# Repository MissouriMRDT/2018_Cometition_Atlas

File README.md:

# 2018_Cometition_Atlas
All Hardware and Software Files used in the 2018 Competition

How to add repos to this while retaining commit history:

1. Clone this repo onto your pc
2. Make branch on here for the repo you're about to copy in
3. Make sure that you've merged the final release branch of the target repo into master
4. In gitshell inside of the 2018 Competition Atlas folder:

git checkout [name of branch you're going to copy the repo into]

git remote add x [url of deprecated repo]

git fetch x

git merge x/master --allow-unrelated-histories

git remote rm x

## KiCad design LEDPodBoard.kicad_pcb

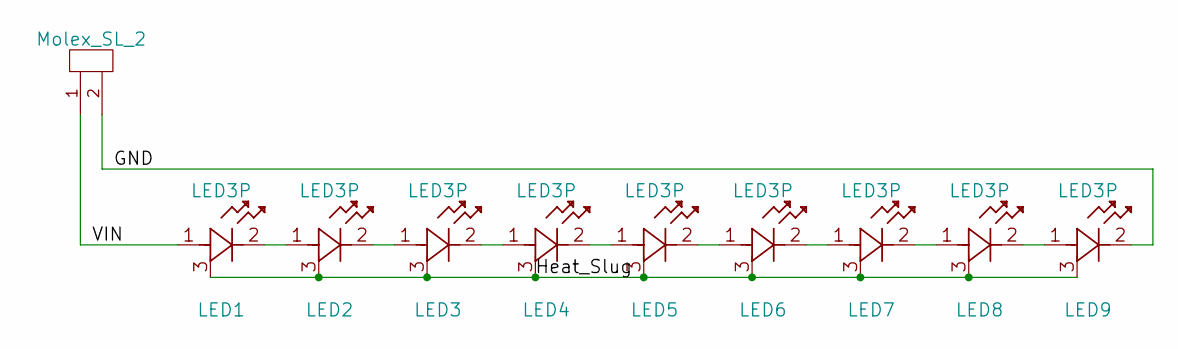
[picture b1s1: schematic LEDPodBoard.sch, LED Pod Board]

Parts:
Conn1: Molex_SL_2; MOLEX_SL_2_Horizontal
LED1, LED2, LED3, LED4, LED5, LED6, LED7, LED8, LED9: LED3P; LED_CREE_XLAMP_XPG

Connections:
/GND: Conn1.2, LED9.2 (Cathode)
/Heat_Slug: LED1.3 (Heat_Dissipation), LED2.3 (Heat_Dissipation), LED3.3 (Heat_Dissipation), LED4.3 (Heat_Dissipation), LED5.3 (Heat_Dissipation), LED6.3 (Heat_Dissipation), LED7.3 (Heat_Dissipation), LED8.3 (Heat_Dissipation), LED9.3 (Heat_Dissipation)
/VIN: Conn1.1, LED1.1 (Anode)
unnamed: LED1.2 (Cathode), LED2.1 (Anode)
unnamed: LED2.2 (Cathode), LED3.1 (Anode)
unnamed: LED3.2 (Cathode), LED4.1 (Anode)
unnamed: LED4.2 (Cathode), LED5.1 (Anode)
unnamed: LED5.2 (Cathode), LED6.1 (Anode)
unnamed: LED6.2 (Cathode), LED7.1 (Anode)
unnamed: LED7.2 (Cathode), LED8.1 (Anode)
unnamed: LED8.2 (Cathode), LED9.1 (Anode)

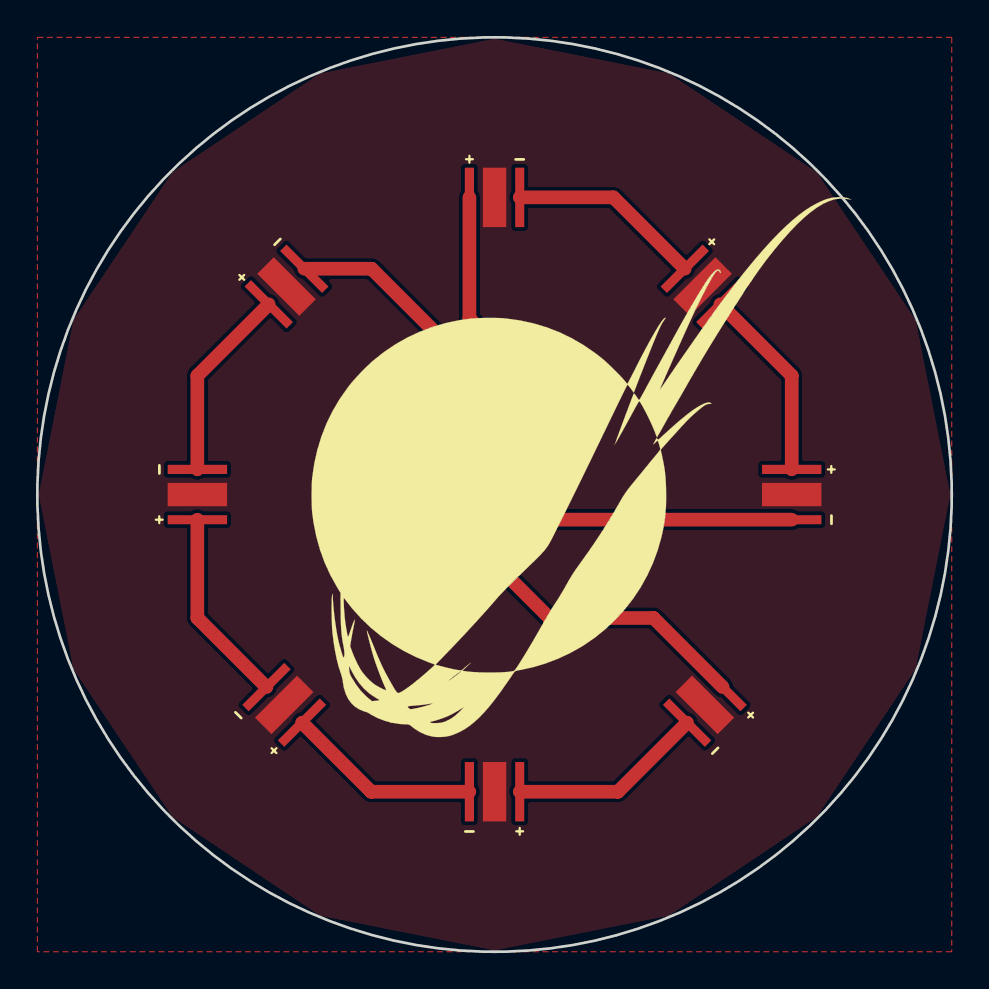
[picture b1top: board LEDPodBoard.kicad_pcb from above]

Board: 2 copper layers, 50.8 x 50.8 mm, 10 parts (1 on the bottom side), 11 nets.

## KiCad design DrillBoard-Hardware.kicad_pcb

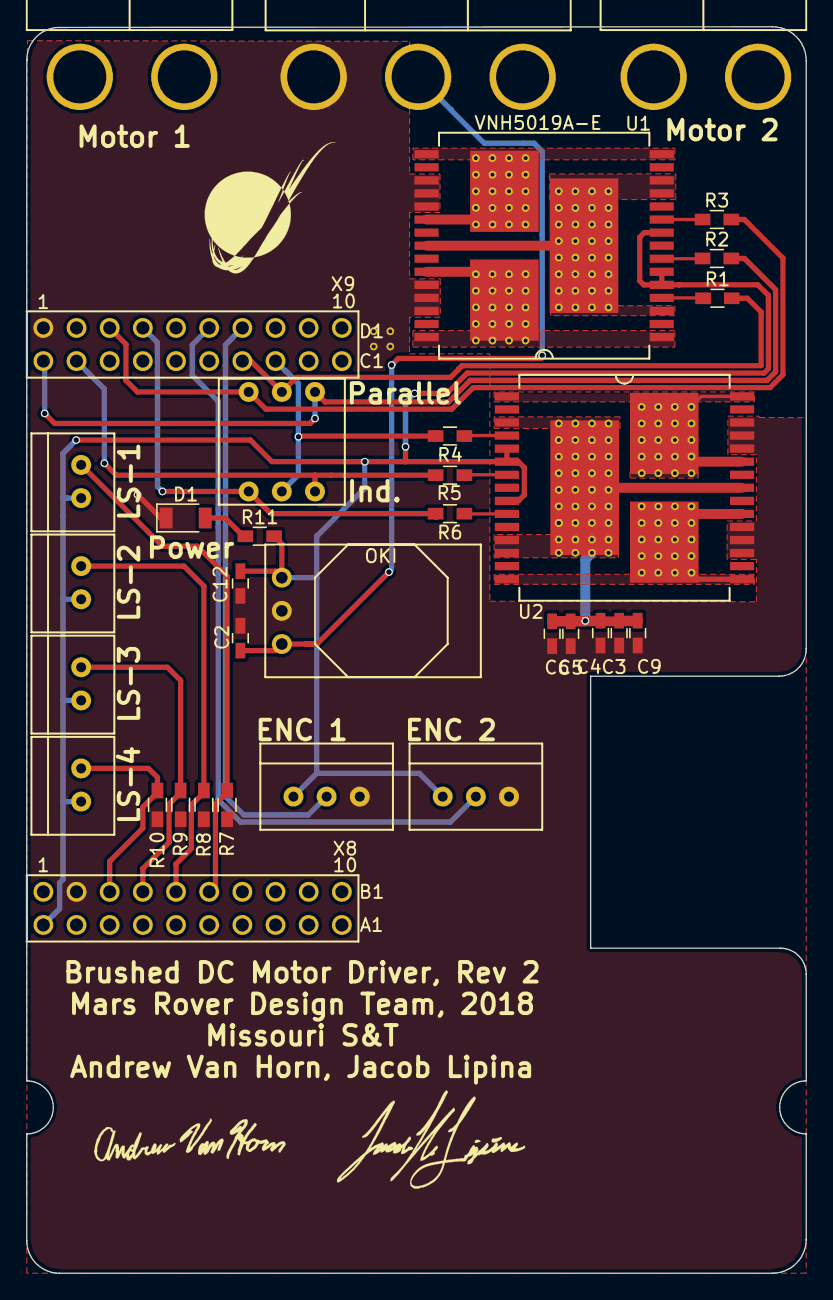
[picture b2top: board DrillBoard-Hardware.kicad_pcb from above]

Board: 2 copper layers, 59.7 x 95.5 mm, 33 parts (0 on the bottom side), 27 nets.

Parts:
C1: Anderson_3; Anderson_3_Horisontal_Side_by_Side
C2, C3, C5, C6, C9, C12: 10u; C_0603_HandSoldering
C4: .1u; C_0603_HandSoldering
C7, C8: Anderson-2; Anderson_2_Horisontal_Side_by_Side
D1: LED; D_1206
R1, R2, R3, R4, R5, R6: 1K; R_0603_HandSoldering
R7, R8, R9, R10: 10K; R_0603_HandSoldering
R11: 330; R_0603_HandSoldering
SW1: 3P1T_Fused; 3P1T_Switch
U1, U2: VNH5019A-E; MultiPowerSO_30
U3: OKI; OKI_Horisontal
U4: LS_1; MOLEX_SL_2_Vertical
U5: LS_2; MOLEX_SL_2_Vertical
U6: TM4C129E_Launchpad_X9
U7, U8: Picoblade-3; MOLEX_SL_3_Vertical
U9: LS_3; MOLEX_SL_2_Vertical
U10: LS_4; MOLEX_SL_2_Vertical

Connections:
+3V3: C12.1, R11.2, U1.5, U1.6, U1.9, U2.5, U2.6, U2.9, U3.3, U4.1, U5.1, U6.+3V3, U7.1, U8.1, U9.1, U10.1
+12V: C1.1, C3.1, C4.1, C5.1, C6.1, C9.1, U1.3, U1.12, U1.13, U1.23, U1.32, U2.3, U2.12, U2.13, U2.23, U2.32
/12V_Logic: C1.2, C2.1, U3.1
/Out_A1: C7.1, U1.1, U1.25, U1.30, U1.31
/Out_A2: C8.1, U2.1, U2.25, U2.30, U2.31
/Out_B1: C7.2, U1.15, U1.16, U1.21, U1.33
/Out_B2: C8.2, U2.15, U2.16, U2.21, U2.33
Encoder1_PWM: U6.PD0, U7.2
Encoder2_PWM: U6.PD1, U8.2
GND: C1.3, C2.2, C3.2, C4.2, C5.2, C6.2, C9.2, C12.2, D1.1, R7.2, R8.2, R9.2, R10.2, U1.18, U1.19, U1.20, U1.26, U1.27, U1.28, U2.18, U2.19, U2.20, U2.26, U2.27, U2.28, U3.2, U6.GND, U7.3, U8.3
IN_A1: R1.2, SW1.3, U6.PL0
IN_A2: R4.2, SW1.4, U6.PL1
IN_B1: R3.2, SW1.1, U6.PH2
IN_B2: R6.2, SW1.2, U6.PH3
LS_1: R7.1, U4.2, U6.PE3
LS_2: R8.1, U5.2, U6.PE2
LS_3: R9.1, U6.PE1, U9.2
LS_4: R10.1, U6.PE0, U10.2
unnamed: D1.2, R11.1
unnamed: R1.1, U1.4
unnamed: R2.1, U1.7
unnamed: R3.1, U1.10
unnamed: R4.1, U2.4
unnamed: R5.1, U2.7
unnamed: R6.1, U2.10
PWM1: R2.2, SW1.5, U6.PF1
PWM2: R5.2, SW1.6, U6.PF2

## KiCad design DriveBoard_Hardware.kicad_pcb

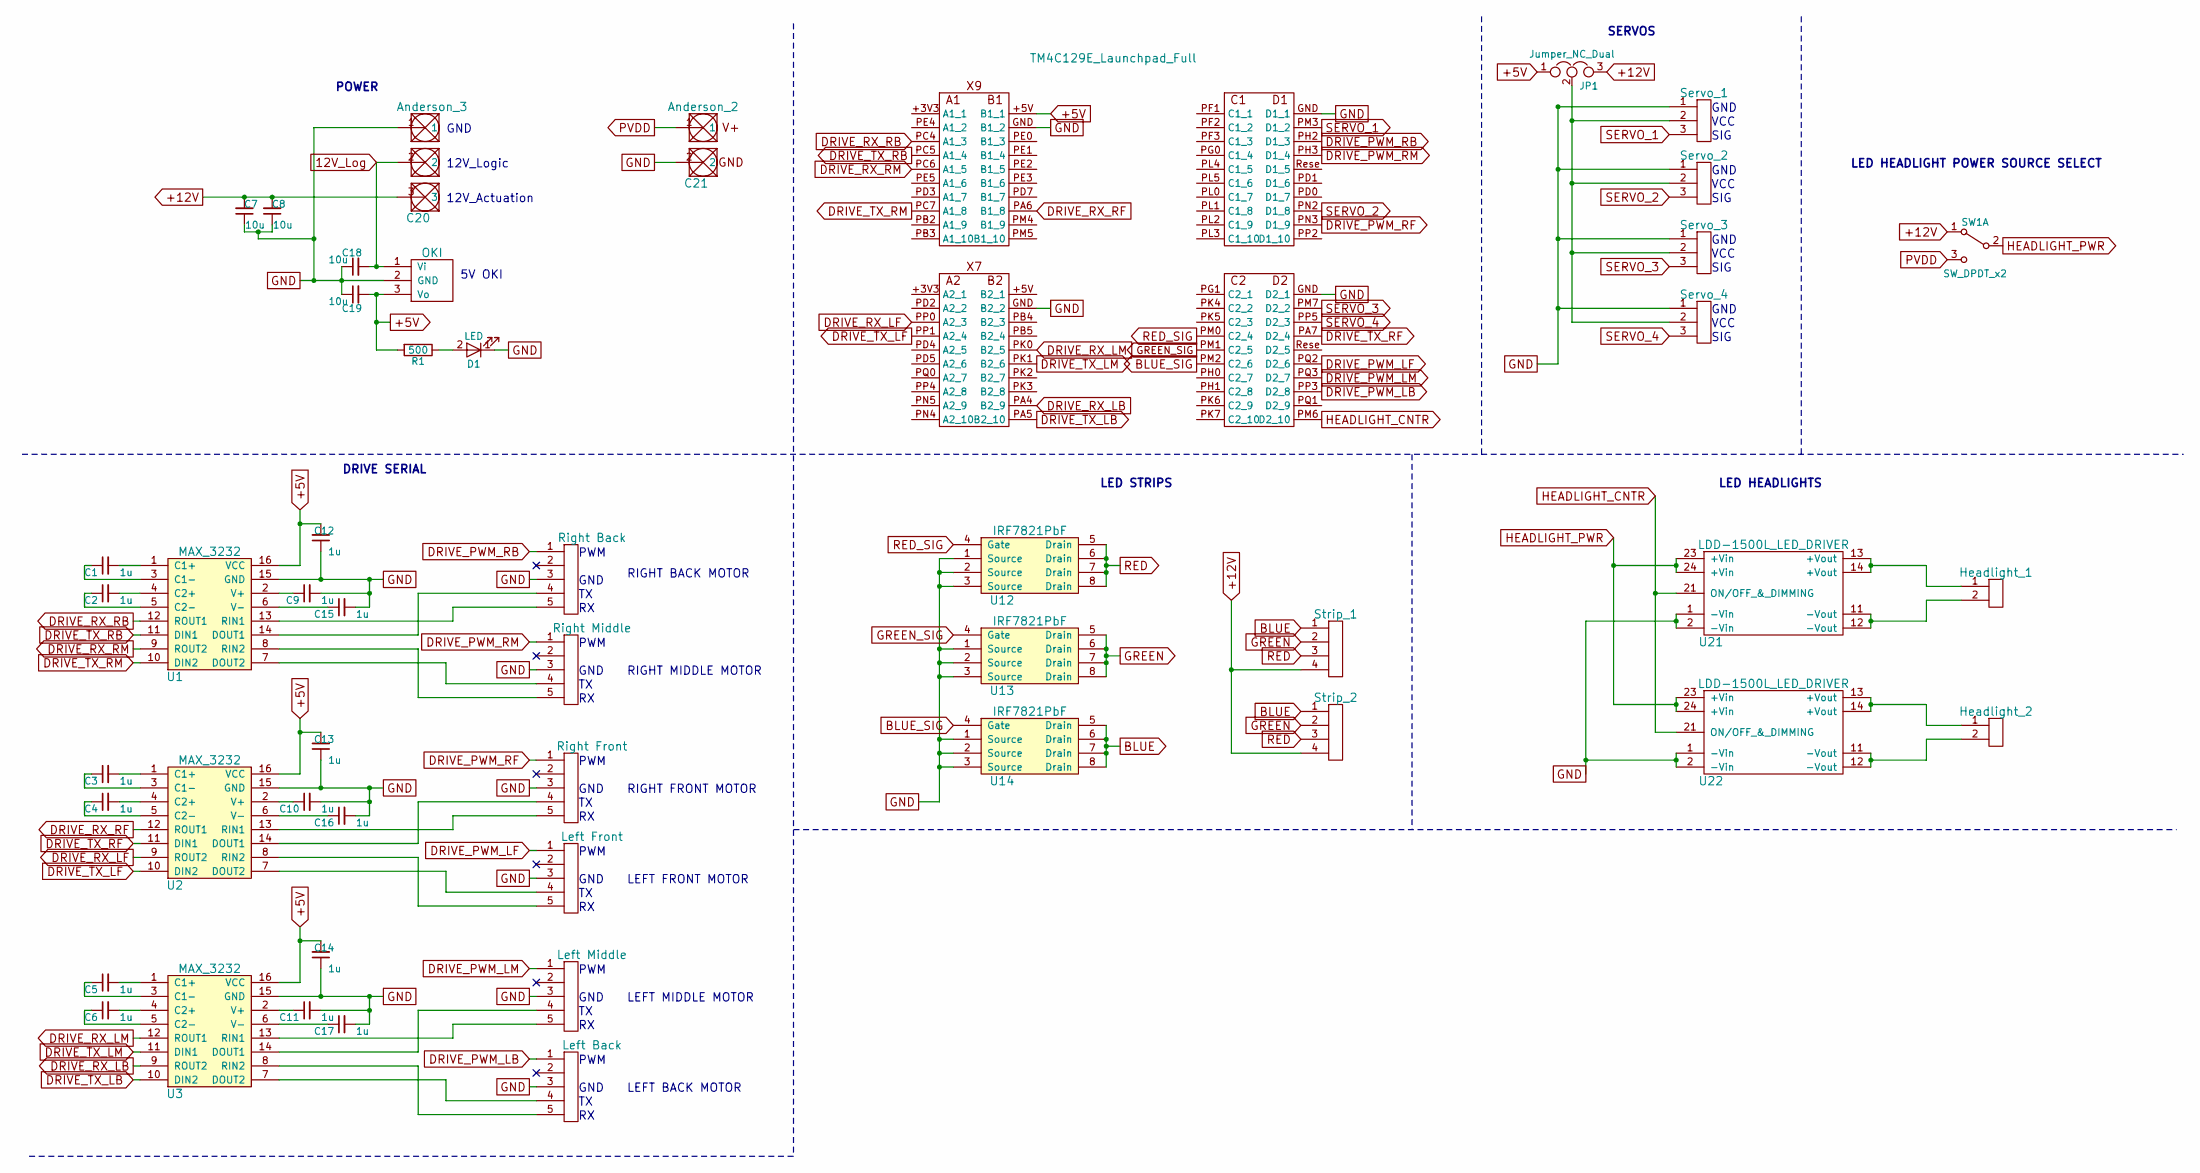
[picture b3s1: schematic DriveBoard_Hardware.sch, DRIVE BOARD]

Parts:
C1, C2, C3, C4, C5, C6, C9, C10, C11, C12, C13, C14, C15, C16, C17: 1u; C_0603_HandSoldering
C7, C8, C18, C19: 10u; C_0603_HandSoldering
C20: Anderson_3; Anderson_3_Horisontal_Side_by_Side
C21: Anderson_2; Anderson_2_Horisontal_Side_by_Side
D1: LED; LED_1206_HandSoldering
JP1: Jumper_NC_Dual; Pin_Header_Angled_1x03_Pitch1.27mm
R1: 500; R_0603_HandSoldering
SW1: SW_DPDT_x2; 1P2T_Angled_Slide_GPI-152-3013
U1, U2, U3: MAX_3232; SOIC_16_3.9x9.9mm_Pitch1.27mm
U4: OKI; OKI_Horisontal
U5: Right Back; MOLEX_SL_5_Horizontal
U6: Right Middle; MOLEX_SL_5_Horizontal
U7: Right Front; MOLEX_SL_5_Horizontal
U8: Left Front; MOLEX_SL_5_Horizontal
U9: Left Middle; MOLEX_SL_5_Horizontal
U10: Left Back; MOLEX_SL_5_Horizontal
U11: TM4C129E_Launchpad_Full; TM4C129E_Launchpad_FULL_Booster_Bottom_SMD
U12, U13, U14: IRF7821PbF; SO-8_5.3x6.2mm_Pitch1.27mm
U15: Strip_1; MOLEX_SL_4_Horizontal
U16: Strip_2; MOLEX_SL_4_Horizontal
U17: Servo_1; MOLEX_SL_3_Vertical
U18: Servo_2; MOLEX_SL_3_Vertical
U19: Servo_3; MOLEX_SL_3_Vertical
U20: Servo_4; MOLEX_SL_3_Vertical
U21, U22: LDD-1500L_LED_DRIVER
U23: Headlight_1; MOLEX_SL_2_Vertical
U24: Headlight_2; MOLEX_SL_2_Vertical

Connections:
12V_Log: C18.2, C20.2, U4.1 (Vi)
+5V: C12.2, C13.2, C14.2, C19.2, JP1.1, R1.2, U1.16 (VCC), U2.16 (VCC), U3.16 (VCC), U4.3 (Vo), U11.+5V (B1_1)
+12V: C7.2, C8.2, C20.3, JP1.3, SW1.1 (A), U15.4, U16.4
BLUE: U14.5 (Drain), U14.6 (Drain), U14.7 (Drain), U14.8 (Drain), U15.1, U16.1
BLUE_SIG: U11.PM2 (C2_6), U14.4 (Gate)
DRIVE_PWM_LB: U10.1, U11.PP3 (D2_8)
DRIVE_PWM_LF: U8.1, U11.PQ2 (D2_6)
DRIVE_PWM_LM: U9.1, U11.PQ3 (D2_7)
DRIVE_PWM_RB: U5.1, U11.PH2 (D1_3)
DRIVE_PWM_RF: U7.1, U11.PN3 (D1_9)
DRIVE_PWM_RM: U6.1, U11.PH3 (D1_4)
DRIVE_RX_LB: U3.9 (ROUT2), U11.PA4 (B2_9)
DRIVE_RX_LF: U2.9 (ROUT2), U11.PP0 (A2_3)
DRIVE_RX_LM: U3.12 (ROUT1), U11.PK0 (B2_5)
DRIVE_RX_RB: U1.12 (ROUT1), U11.PC4 (A1_3)
DRIVE_RX_RF: U2.12 (ROUT1), U11.PA6 (B1_8)
DRIVE_RX_RM: U1.9 (ROUT2), U11.PC6 (A1_5)
DRIVE_TX_LB: U3.10 (DIN2), U11.PA5 (B2_10)
DRIVE_TX_LF: U2.10 (DIN2), U11.PP1 (A2_4)
DRIVE_TX_LM: U3.11 (DIN1), U11.PK1 (B2_6)
DRIVE_TX_RB: U1.11 (DIN1), U11.PC5 (A1_4)
DRIVE_TX_RF: U2.11 (DIN1), U11.PA7 (D2_4)
DRIVE_TX_RM: U1.10 (DIN2), U11.PC7 (A1_8)
GND: C7.1, C8.1, C9.2, C10.2, C11.2, C12.1, C13.1, C14.1, C15.2, C16.2, C17.2, C18.1, C19.1, C20.1, C21.2, D1.1 (K), U1.15 (GND), U2.15 (GND), U3.15 (GND), U4.2 (GND), U5.3, U6.3, U7.3, U8.3, U9.3, U10.3, U11.GND (B1_2), U12.1 (Source), U12.2 (Source), U12.3 (Source), U13.1 (Source), U13.2 (Source), U13.3 (Source), U14.1 (Source), U14.2 (Source), U14.3 (Source), U17.1, U18.1, U19.1, U20.1, U21.1 (-Vin), U21.2 (-Vin), U22.1 (-Vin), U22.2 (-Vin)
GREEN: U13.5 (Drain), U13.6 (Drain), U13.7 (Drain), U13.8 (Drain), U15.2, U16.2
GREEN_SIG: U11.PM1 (C2_5), U13.4 (Gate)
HEADLIGHT_CNTR: U11.PM6 (D2_10), U21.21 (ON/OFF_&_DIMMING), U22.21 (ON/OFF_&_DIMMING)
HEADLIGHT_PWR: SW1.2 (B), U21.23 (+Vin), U21.24 (+Vin), U22.23 (+Vin), U22.24 (+Vin)
unnamed: C1.1, U1.3 (C1-)
unnamed: C1.2, U1.1 (C1+)
unnamed: C2.1, U1.5 (C2-)
unnamed: C2.2, U1.4 (C2+)
unnamed: C3.1, U2.3 (C1-)
unnamed: C3.2, U2.1 (C1+)
unnamed: C4.1, U2.5 (C2-)
unnamed: C4.2, U2.4 (C2+)
unnamed: C5.1, U3.3 (C1-)
unnamed: C5.2, U3.1 (C1+)
unnamed: C6.1, U3.5 (C2-)
unnamed: C6.2, U3.4 (C2+)
unnamed: C9.1, U1.2 (V+)
unnamed: C10.1, U2.2 (V+)
unnamed: C11.1, U3.2 (V+)
unnamed: C15.1, U1.6 (V-)
unnamed: C16.1, U2.6 (V-)
unnamed: C17.1, U3.6 (V-)
unnamed: D1.2 (A), R1.1
unnamed: JP1.2, U17.2, U18.2, U19.2, U20.2
unnamed: U1.7 (DOUT2), U6.4
unnamed: U1.8 (RIN2), U6.5
unnamed: U1.13 (RIN1), U5.5
unnamed: U1.14 (DOUT1), U5.4
unnamed: U2.7 (DOUT2), U8.4
unnamed: U2.8 (RIN2), U8.5
unnamed: U2.13 (RIN1), U7.5
unnamed: U2.14 (DOUT1), U7.4
unnamed: U3.13 (RIN1), U9.5
unnamed: U3.14 (DOUT1), U9.4
unnamed: U3.7 (DOUT2), U10.4
unnamed: U3.8 (RIN2), U10.5
unnamed: U21.11 (-Vout), U21.12 (-Vout), U23.2
unnamed: U21.13 (+Vout), U21.14 (+Vout), U23.1
unnamed: U22.11 (-Vout), U22.12 (-Vout), U24.2
unnamed: U22.13 (+Vout), U22.14 (+Vout), U24.1
PVDD: C21.1, SW1.3 (C)
RED: U12.5 (Drain), U12.6 (Drain), U12.7 (Drain), U12.8 (Drain), U15.3, U16.3
RED_SIG: U11.PM0 (C2_4), U12.4 (Gate)
SERVO_1: U11.PM3 (D1_2), U17.3
SERVO_2: U11.PN2 (D1_8), U18.3
SERVO_3: U11.PM7 (D2_2), U19.3
SERVO_4: U11.PP5 (D2_3), U20.3

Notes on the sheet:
GND
12V_Logic
12V_Actuation
5V OKI
POWER
PWM
RIGHT BACK MOTOR
RIGHT MIDDLE MOTOR
RIGHT FRONT MOTOR
LEFT FRONT MOTOR
LEFT MIDDLE MOTOR
LEFT BACK MOTOR
DRIVE SERIAL
VCC
SIG
SERVOS
LED STRIPS
LED HEADLIGHTS
LED HEADLIGHT POWER SOURCE SELECT

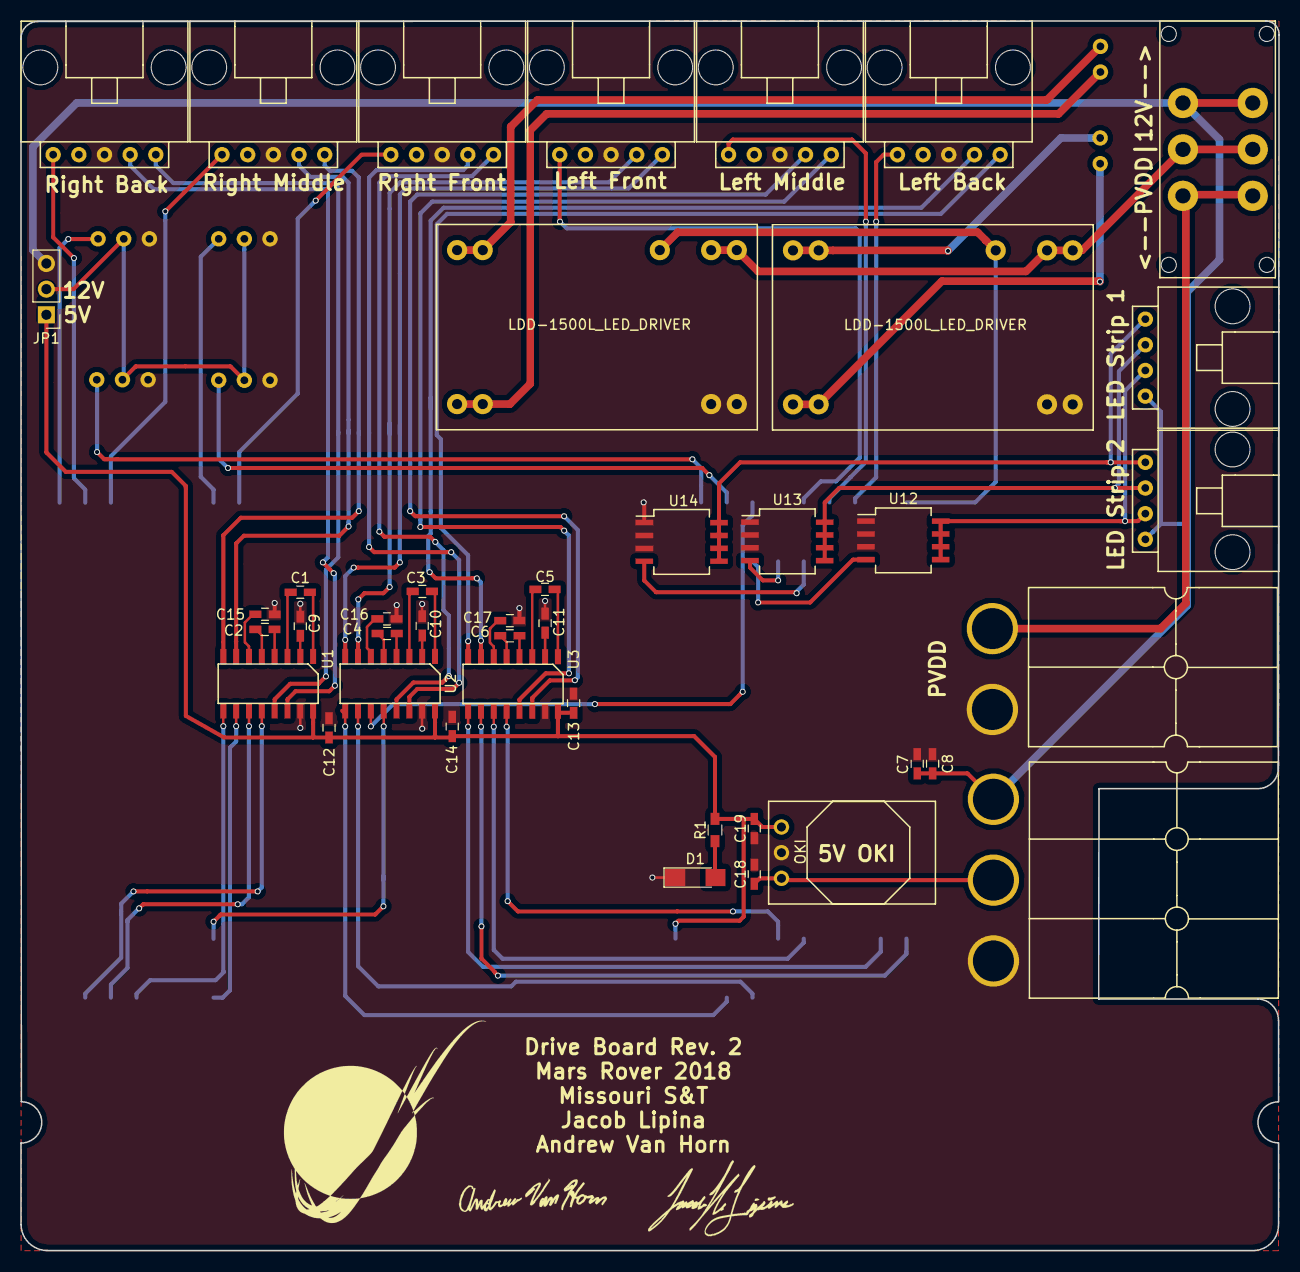
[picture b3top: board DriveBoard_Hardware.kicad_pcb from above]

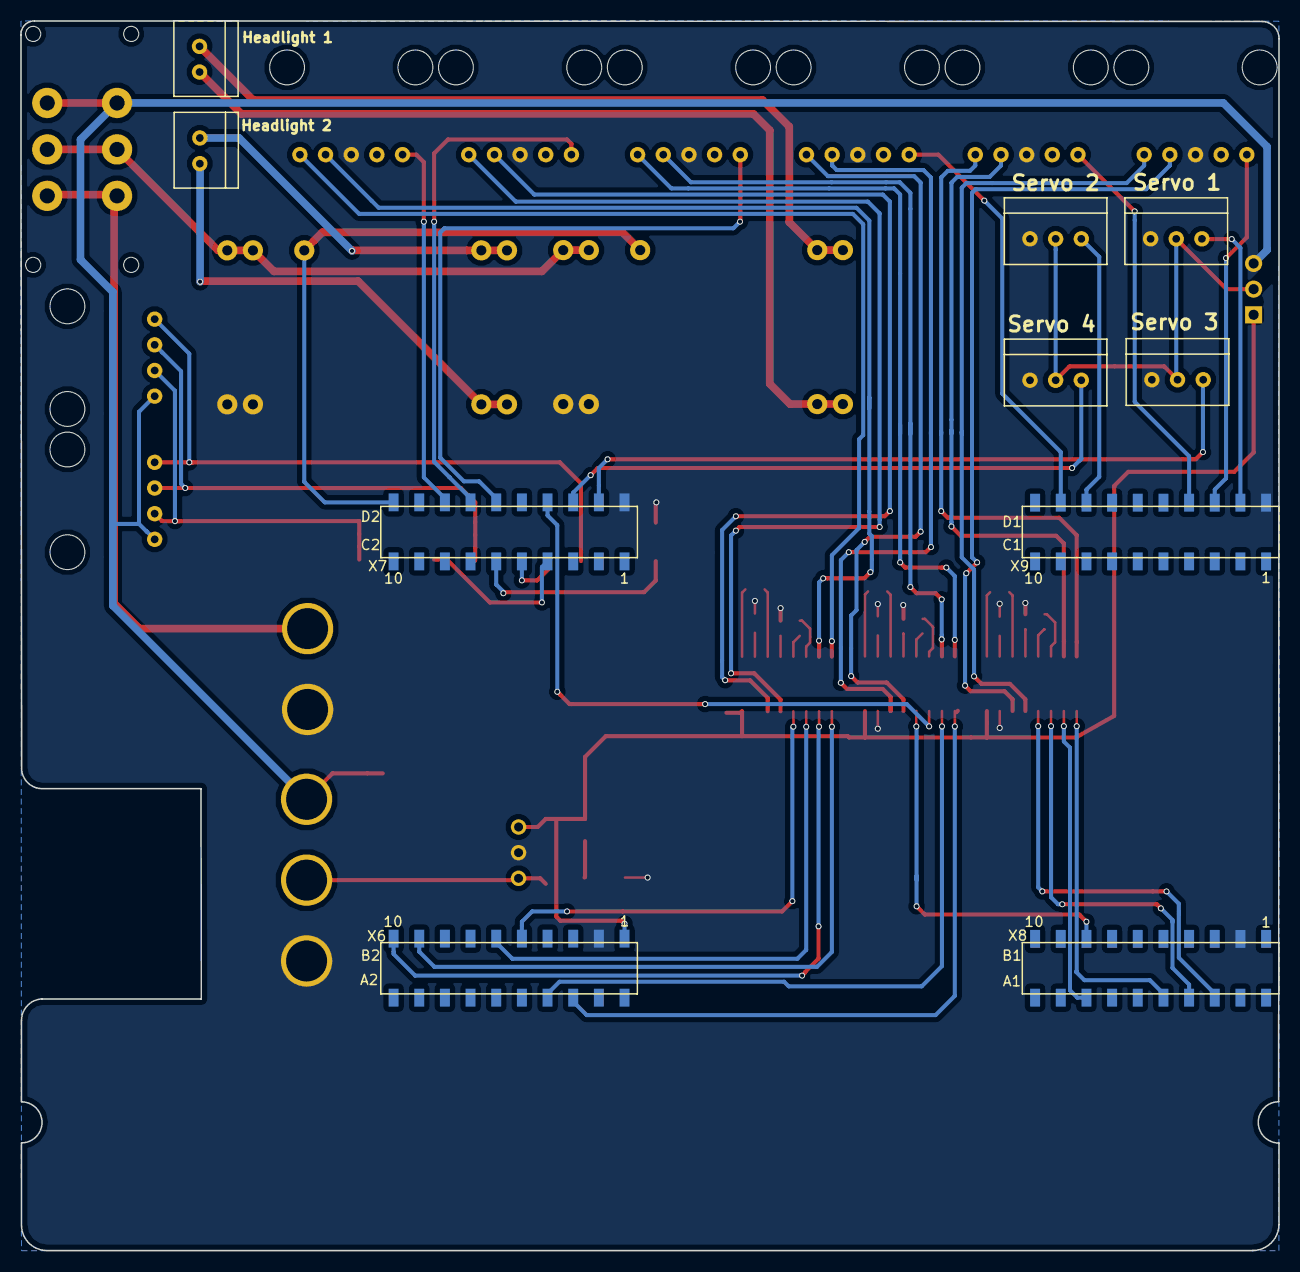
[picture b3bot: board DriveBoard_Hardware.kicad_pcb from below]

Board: 2 copper layers, 124.5 x 121.7 mm, 49 parts (6 on the bottom side), 71 nets.

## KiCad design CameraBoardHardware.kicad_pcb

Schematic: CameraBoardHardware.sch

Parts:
C2, C3, C4, C5, C6, C7, C9, C10, C11, C12, C13, C14, C15, C16, C17: 10uf; C_0603_HandSoldering
C8: Anderson_3; Anderson_3_Horisontal_Side_by_Side
C18, C19, C20: 0.1uf; C_0603_HandSoldering
D1: LED; LED_0603_HandSoldering
J1: BNC_75_OHM_HORIZ; BNC-75-Ohm-HORIZONTAL-1-1478032-0
J2, J3, J4, J5: BNC_75_OHM_HORIZ; bnc-ci
R1, R2, R3, R4, R9: 75; R_0603_HandSoldering
R5: 330; R_0603_HandSoldering
R6: 100k; R_0603_HandSoldering
R7, R8: 470; R_0603_HandSoldering
U1, U2, U3, U4, U14: Picoblade_3; Molex_PicoBlade_53047-0310_03x1.25mm_Straight
U5, U6, U7, U8: Molex_SL_3; MOLEX_SL_3_Vertical
U9: OKI; OKI_Horisontal
U10: LMH6574MA; LMH6574MA&slash_NOPB
U11: TM4C129E_Launchpad_X7; TM4C129E_Launchpad_X7_Bottom_SMD
U12: TXB0102_DCU_8; TXB0102DCUR
U13: Molex_SL_3; MOLEX_SL_3_Horizontal

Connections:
3.3V: C2.1, C5.1, C9.1, C12.1, C15.1, C18.1, R5.2, R6.2, U11.+3V3, U12.3
5V: C3.1, C6.1, C10.1, C13.1, C16.1, C19.1, U9.3 (Vo), U11.+5V, U12.7
12V: C4.1, C7.1, C8.2, C11.1, C14.1, C17.1, C20.1, U1.3, U2.3, U3.3, U4.3, U5.3, U6.3, U7.3, U8.3, U9.1 (Vi), U10.14, U13.2, U14.2
12VA: C8.3, U13.1, U14.3
A1: U11.PK4, U12.5
A2: U11.PK5, U12.4
B1: U10.8, U12.8
B2: U10.9, U12.1
Camera1_In: J4.1, R1.1, U4.1, U8.1, U10.1
Camera2_In: J3.1, R2.1, U3.1, U7.1, U10.3
Camera3_In: J2.1, R3.1, U2.1, U6.1, U10.5
Camera4_In: J5.1, R4.1, U1.1, U5.1, U10.7
Gnd: C2.2, C3.2, C4.2, C5.2, C6.2, C7.2, C8.1, C9.2, C10.2, C11.2, C12.2, C13.2, C14.2, C15.2, C16.2, C17.2, C18.2, C19.2, C20.2, D1.1 (K), J1.2, J2.2, J3.2, J4.2, J5.2, R1.2, R2.2, R3.2, R4.2, R6.1, R8.2, U1.2, U2.2, U3.2, U4.2, U5.2, U6.2, U7.2, U8.2, U9.2 (GND), U10.2, U10.4, U10.6, U10.10, U10.11, U11.GND, U12.2, U13.3, U14.1
unnamed: D1.2 (A), R5.1
unnamed: R7.1, R9.1, U10.13
unnamed: R7.2, R8.1, U10.12
OE: U11.PG1, U12.6
Video_Out: J1.1, R9.2

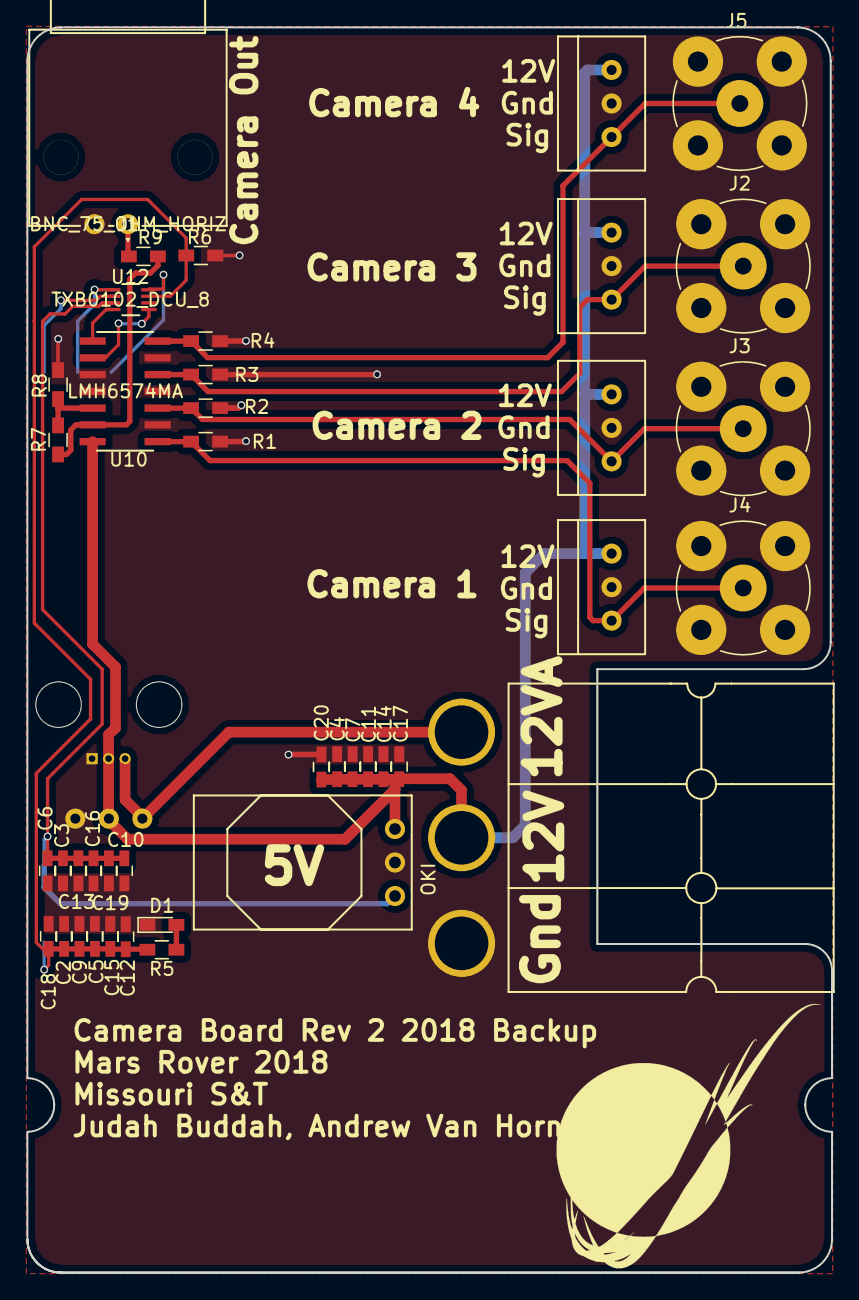
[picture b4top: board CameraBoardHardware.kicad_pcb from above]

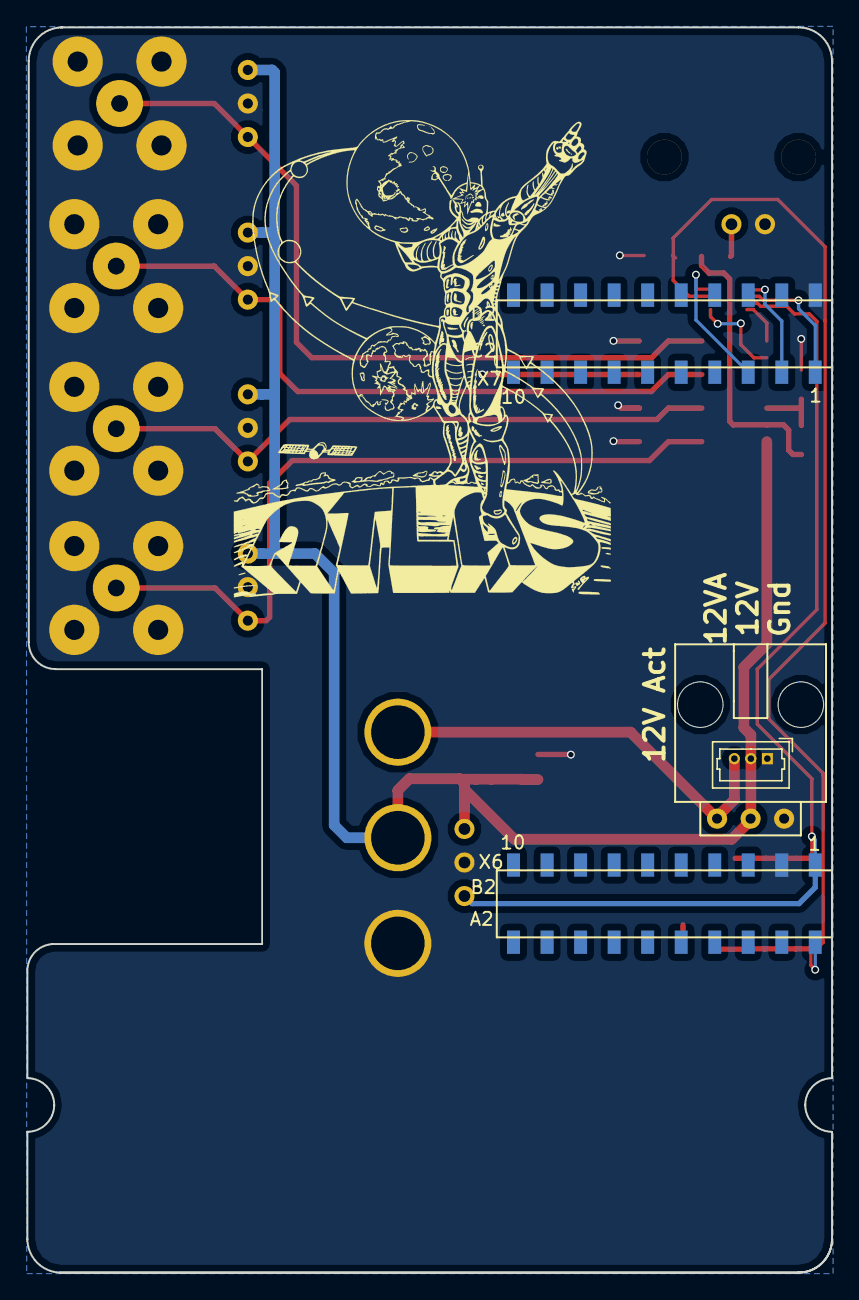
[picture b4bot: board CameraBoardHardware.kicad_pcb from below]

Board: 2 copper layers, 61.0 x 94.3 mm, 44 parts (2 on the bottom side), 18 nets.

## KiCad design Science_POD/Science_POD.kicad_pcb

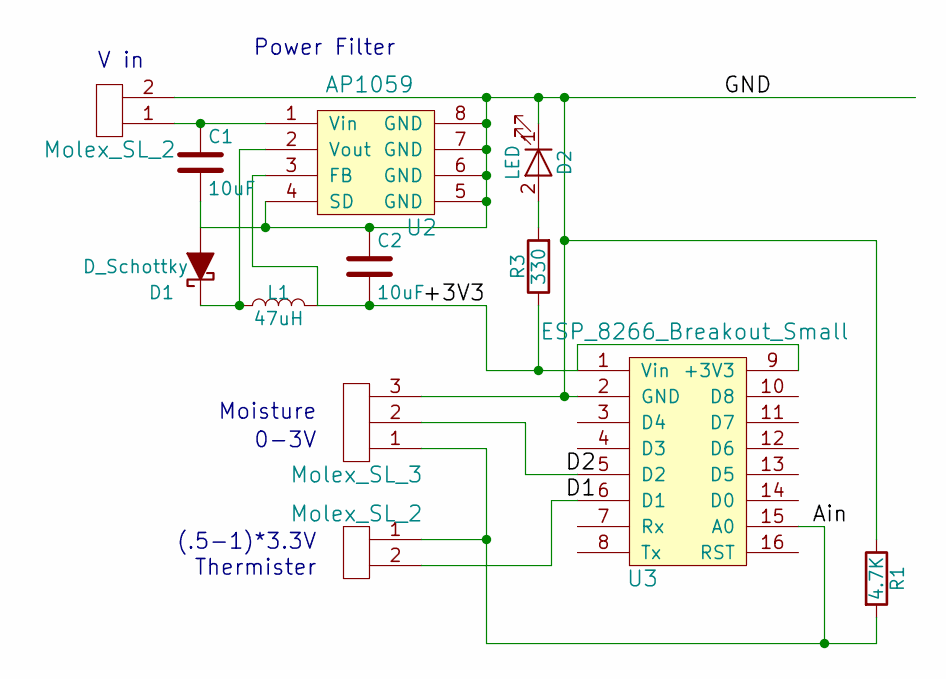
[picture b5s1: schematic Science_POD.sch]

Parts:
C1, C2: 10uF; C_0603_HandSoldering
Conn1: Molex_SL_2; MOLEX_SL_2_Horizontal
D1: D_Schottky; C_0603_HandSoldering
D2: LED; D_1206
L1: 47uH; L_0603_HandSoldering
R1: 4.7K; R_0603_HandSoldering
R3: 330; R_0603_HandSoldering
U1: Molex_SL_2; MOLEX_SL_2
U2: AP1059; HTSOP-8-1EP_3.9x4.9mm_Pitch1.27mm
U3: ESP_8266_Breakout_Small
U4: Molex_SL_3; MOLEX_SL_3

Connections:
/+3V3: C2.2, L1.2, R3.1, U2.3 (FB), U3.1 (Vin), U3.9 (+3V3)
/Ain: Conn1.1, R1.2, U3.15 (A0), U4.1
/D1: Conn1.2, U3.6 (D1)
/D2: U3.5 (D2), U4.2
/GND: C1.2, C2.1, D1.2 (A), D2.1 (K), R1.1, U1.2, U2.4 (SD), U2.5 (GND), U2.6 (GND), U2.7 (GND), U2.8 (GND), U3.2 (GND), U4.3
unnamed: C1.1, U1.1, U2.1 (Vin)
unnamed: D1.1 (K), L1.1, U2.2 (Vout)
unnamed: D2.2 (A), R3.2

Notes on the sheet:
V in
Power Filter
Thermister
Moisture
(.5-1)*3.3V
0-3V

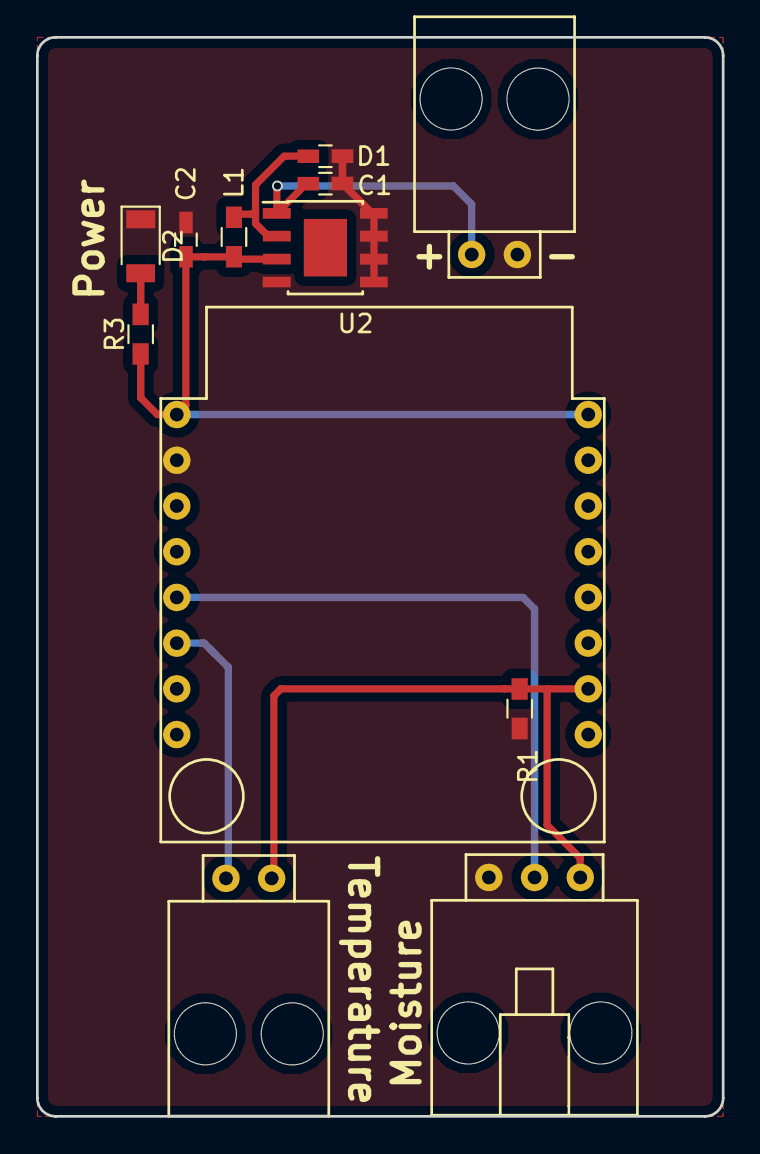
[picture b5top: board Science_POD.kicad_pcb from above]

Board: 2 copper layers, 38.1 x 59.9 mm, 12 parts (0 on the bottom side), 8 nets.

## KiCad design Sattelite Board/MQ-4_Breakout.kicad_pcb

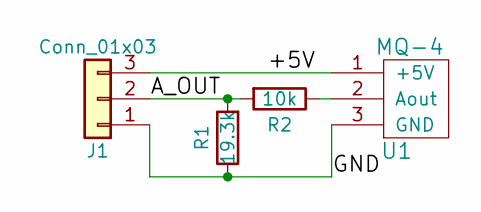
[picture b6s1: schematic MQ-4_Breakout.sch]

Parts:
J1: Conn_01x03; 3x1_Header
R1: 19.3k; R_0603_HandSoldering
R2: 10k; R_0603_HandSoldering
U1: MQ-4

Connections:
/+5V: J1.3, U1.1 (+5V)
/A_OUT: J1.2, R1.2, R2.2
/GND: J1.1, R1.1, U1.3 (GND)
unnamed: R2.1, U1.2 (Aout)

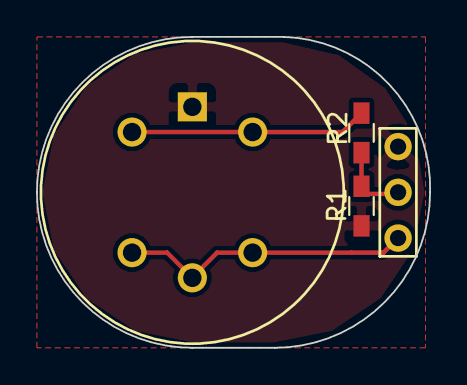
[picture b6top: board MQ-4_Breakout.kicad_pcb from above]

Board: 2 copper layers, 21.8 x 17.3 mm, 4 parts (0 on the bottom side), 4 nets.

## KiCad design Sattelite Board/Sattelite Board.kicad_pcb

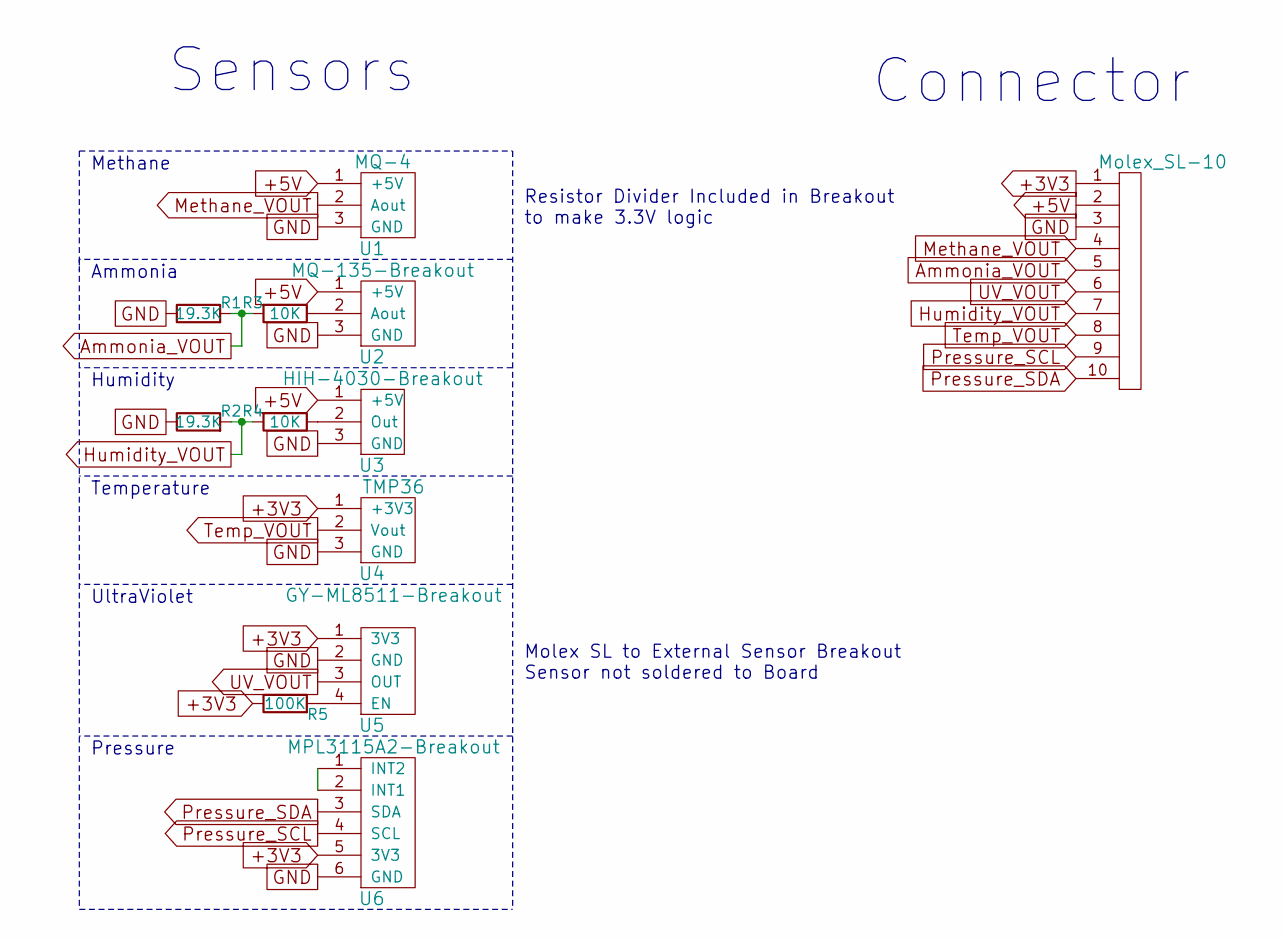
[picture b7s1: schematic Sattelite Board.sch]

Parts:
R1, R2: 19.3K; R_0603_HandSoldering
R3, R4: 10K; R_0603_HandSoldering
R5: 100K; R_0603_HandSoldering
U1: MQ-4; MQ-4-Breakout
U2: MQ-135-Breakout
U3: HIH-4030-Breakout
U4: TMP36; TMP36-Breakout
U5: GY-ML8511-Breakout
U6: MPL3115A2-Breakout
U7: Molex_SL-10; MOLEX_SL_10

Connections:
+3V3: R5.1, U4.1 (+3V3), U5.1 (3V3), U6.5 (3V3), U7.1
+5V: U1.1 (+5V), U2.1 (+5V), U3.1 (+5V), U7.2
Ammonia_VOUT: R1.2, R3.2, U7.5
GND: R1.1, R2.1, U1.3 (GND), U2.3 (GND), U3.3 (GND), U4.3 (GND), U5.2 (GND), U6.6 (GND), U7.3
Humidity_VOUT: R2.2, R4.2, U7.7
Methane_VOUT: U1.2 (Aout), U7.4
unnamed: R3.1, U2.2 (Aout)
unnamed: R4.1, U3.2 (Out)
unnamed: R5.2, U5.4 (EN)
unnamed: U6.1 (INT2), U6.2 (INT1)
Pressure_SCL: U6.4 (SCL), U7.9
Pressure_SDA: U6.3 (SDA), U7.10
Temp_VOUT: U4.2 (Vout), U7.8
UV_VOUT: U5.3 (OUT), U7.6

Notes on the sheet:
Sensors
Methane
Connector
Ammonia
Humidity
Temperature
UltraViolet
Pressure
Resistor Divider Included in Breakout to make 3.3V logic
Molex SL to External Sensor Breakout Sensor not soldered to Board

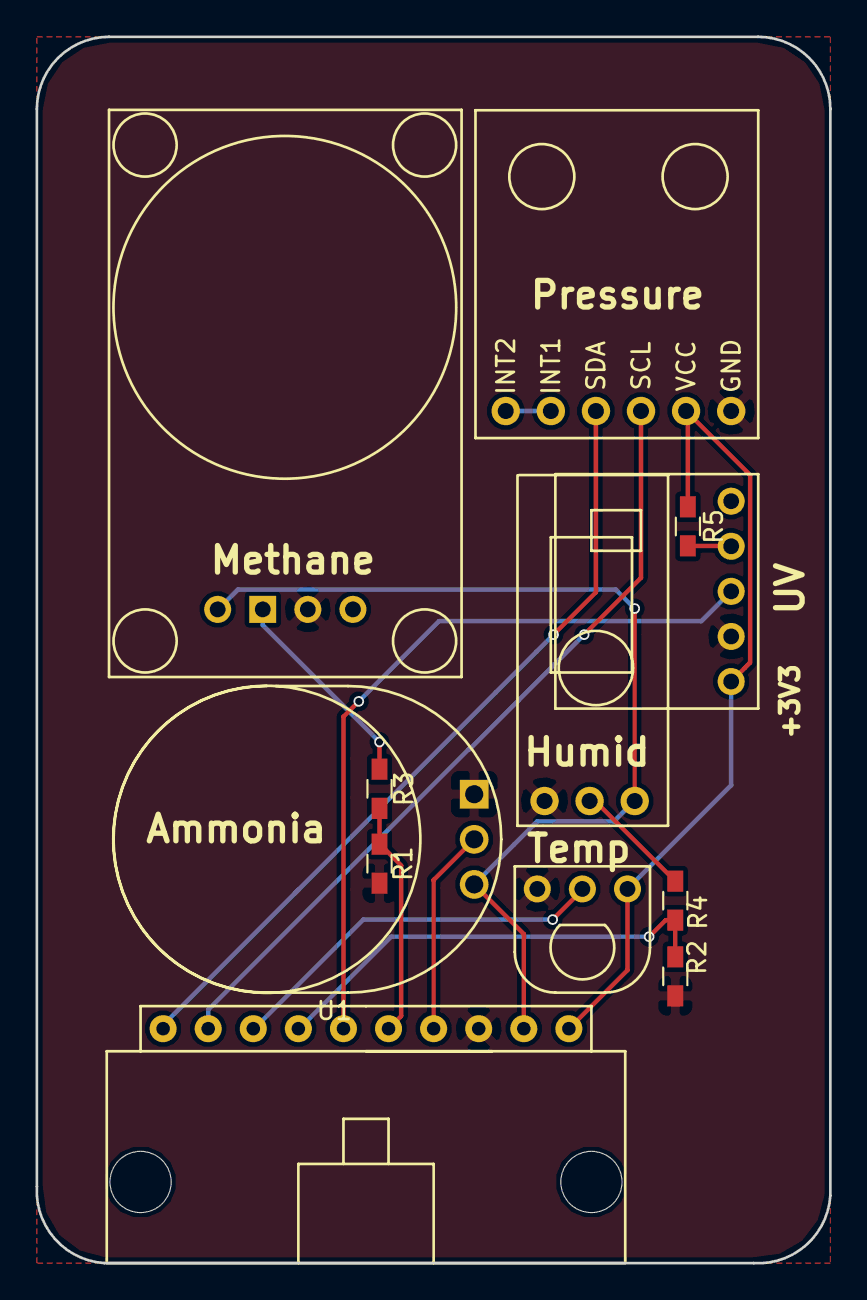
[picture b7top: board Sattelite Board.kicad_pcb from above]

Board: 2 copper layers, 44.7 x 69.1 mm, 12 parts (0 on the bottom side), 14 nets.

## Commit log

2018-07-13 IK-ModelDevelopment
2018-07-13 GimbalBoard Software
2018-07-13 ScienceSattelite-Hardware
2018-07-13 RoveWare
2018-07-13 RoveBoard
2018-07-13 BmsBoardSoftware
2018-07-13 PowerBoardSoftware
2018-07-13 SensorPodSoftware
2018-07-13 NavBoardSoftware
2018-07-13 DrillBoardSoftware
2018-07-13 DriveBoardSoftware
2018-07-13 ScienceBoardSoftware
2018-07-13 ArmBoardSoftware
2018-07-13 AutonomyBoard-Software
2018-07-13 RoveWareEnergia
2018-07-13 CameraBoarSoftware
2018-07-13 SensorPod-Hardware
2018-07-13 CameraBoardHardware
2018-07-13 ArmBoardHardware
2018-07-13 DriveBoardhardware
2018-07-13 DrillBoard-Hardware
2018-07-13 NavBoard-Hardware
2018-07-13 KiCAD-Libraries-Hardware
2018-07-13 BMS-Charger-Hardware
2018-07-13 LEDPodBoadHardware
2018-07-13 ScienceBoard-ardware
2018-07-13 RoveBoardESP8266
2018-07-13 Power-Patch-Panel-Hardware
2018-07-13 PowerBoard-Hardware
2018-07-13 Motor-Controller-Hardware
2018-07-13 Eagle-Libraries-Hardware
2018-07-23 Drue's Modifications
2018-07-23 updated NavBoard
2019-03-25 Removed unnecesary motorware
2019-07-07 Update README.md
    added documentation on merging branches with commit history
2019-07-07 fixed numbering
2019-07-09 Removed depricated systems

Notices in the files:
parts and their libraries:
Copyright 2016 Accelerated Designs. All rights reserved.
